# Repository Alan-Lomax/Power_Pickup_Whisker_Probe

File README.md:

# Power Pickup Whisker Probe
Is a very small PCB board using only a couple of components (one LED and one resistor)
It is a simple voltage tester for use on the model railway.
Using the whiskers it can also be used to inject power to a specfic wheel set 
on a loco and thus used to detect loose, dirty, or ill fitting pickup contacts.

## Key Features
<Li>Reliable clear indication of power and polarity
<Li>Inexpensive and easy to build
<Li>DC or DCC operation
<Li>Test track, loco pickups, slow action DC motor switching

## Status of Development 
### Only one Prototype Version so Far

## Known Issues
<Li>None

## Thoughts for Improvement
<Li>Add a footprint for a terminal block

# The Panel Version
The PCB is sized less than 20mmm x 20 mm which means it can easily be panelized
in sets of 25. This makes the panelized PCB fit on a single 100mm x 100mm 
PCB which is the normal 'minimum size' for billing. 
Be Aware as the minimum board order quantity is 5 you would get 125 
Power Pickup Whisker Probe PCB's.

There is a seperate folder containing the Panelized version of the Gerbers.

As the individual PCB is small you could consider adding the 
Power Pickup Whisker Probe PCB to another PCB that you may be
ordering anyway.

# Be Aware
Normally all EDITS should be done to the 'single PCB' and then it be repanelized
To repanelize you start a new Kicad project (one with no contents)
and run a 'plug in' to panelize things. You will specfiy which other 
file has the PCB layout you want to panelize. 
You also set the number of rows (5) and collumns (5)
The only manual step needed is to add several straight edge to edge lines
(on the edge cut layer) to separate the individual test boards.
These will be intepreted as 'Vee-Cut' lines and allows separating the two PCBs easily.

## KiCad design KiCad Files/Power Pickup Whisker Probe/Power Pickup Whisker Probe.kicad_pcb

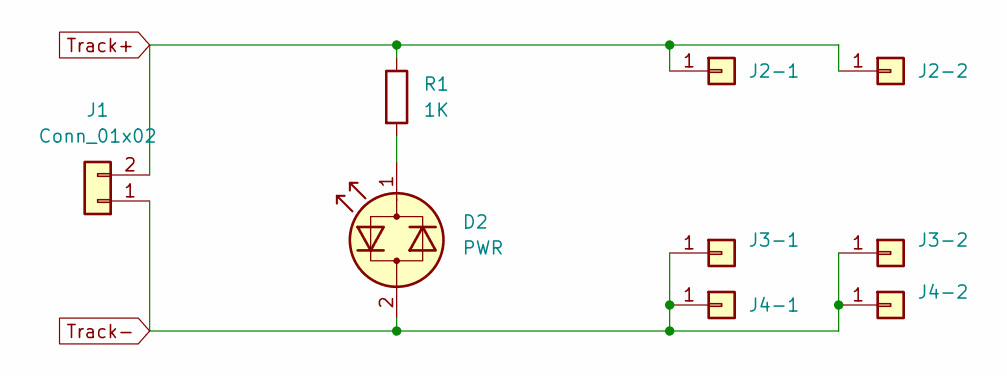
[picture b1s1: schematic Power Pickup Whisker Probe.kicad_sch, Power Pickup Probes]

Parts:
D2: PWR; LED_D5.0mm
J1: Conn_01x02; PinHeader_1x02_P2.54mm_Vertical
J2-1: Com; PinHeader_1x01_P2.54mm_Vertical
J2-2, J3-2, J4-2: Conn_01x01; PinHeader_1x01_P2.54mm_Vertical
J3-1: N; PinHeader_1x01_P2.54mm_Vertical
J4-1: HO/OO; PinHeader_1x01_P2.54mm_Vertical
R1: 1K; R_Axial_DIN0207_L6.3mm_D2.5mm_P7.62mm_Horizontal

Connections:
unnamed: D2.1 (KA), R1.2
Track+: J1.2, J2-1.1, J2-2.1, R1.1
Track-: D2.2 (AK), J1.1, J3-1.1, J3-2.1, J4-1.1, J4-2.1

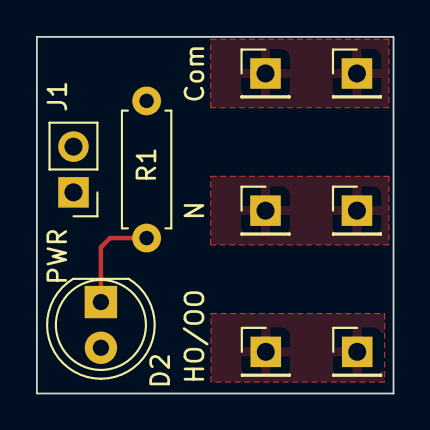
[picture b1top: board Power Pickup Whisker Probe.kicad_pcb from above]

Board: 2 copper layers, 19.8 x 19.8 mm, 9 parts (0 on the bottom side), 3 nets.

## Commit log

2024-01-10 Initial Upload
    Prototype PCB
2024-01-10 Create LICENSE
